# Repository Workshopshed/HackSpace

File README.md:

# HackSpace

Files to go with the Tutorials on HackSpace Magazine

## XMAS

Building a Bluetooth remote controlled Christmas light show

This project combines simple woodworking with electronics to produce a remote control Christmas decoration. Get yourself in the Christmas spirit from the comfort of your own armchair. The skills and techniques of this project can be used in a wide range of other projects.
The decoration is in the form of the 4 letters of XMAS. These are filled with green and red LEDs which are controlled by an Arduino.

https://hackspace.raspberrypi.org/issues/1

## MUSIC BOX

Marvellous mechanical music box

Another combination of woodwork and electronics, this time with no coding. Two 555 timers provide a monostable and astable to control a modified servo to drive a mechanical music mechanism. The stripboard design was done using KiCAD based on the following article.

https://hackspace.raspberrypi.org/issues/2 + https://hackspace.raspberrypi.org/features/the-book-of-making-volumn-1-out-now

https://hobbylad.wordpress.com/2013/04/26/designing-professional-looking-stripboards-using-kicad/ 

## GRINDER BOX

A silver soldered metal storage box to stop my angle grinder cables from being nibbled by mice.
Designed in Fusion360 and build using simple hand tools.

Font stencil from Jayde Garrow 
https://www.dafont.com/army-rust.font

https://hackspace.raspberrypi.org/issues/3 + https://hackspace.raspberrypi.org/features/the-book-of-making-volumn-1-out-now

## HACK SPACE SIGN

An EL Wire sign that lights up when there are people moving about in the room
Controlled using CircuitPython and an AdaFruit Trinket
Ultrabright EL Wire and drivers from EL Wire Craft

https://learn.adafruit.com/adafruit-trinket-m0-circuitpython-arduino/overview

https://hackspace.raspberrypi.org/issues/7 + https://hackspace.raspberrypi.org/features/the-book-of-making-volumn-1-out-now

## ROBOTIC WATER SENTRY

The robot water sentry uses the Google AIY Vision kit to detect humans an squirt them with water.

To make it easy to turn on and off there's a Pimoroni On/Off shim. After further research it was concluded that the default installer for this works just fine.

https://shop.pimoroni.com/products/onoff-shim

https://hackspace.raspberrypi.org/issues/9 + https://hackspace.raspberrypi.org/features/the-book-of-making-volumn-1-out-now

See also https://github.com/Workshopshed/JumboServo

## MONKEY SKULL BOWL

A simple project using the AdaFruit Gemma M0. Take care not to burn yourself when making the jewelled LED eyes.

https://hackspace.raspberrypi.org/issues/12

## KNIFE SWITCH

Unleash your inner mad scientist with this remote controlled knife switch. Using an Energenie remote control.

https://github.com/learn2develop/Arduino_Energenie_Pimote

https://hackspace.raspberrypi.org/issues/13

## ROUTER TRAY

When working with small components one of the best ways to store them for easy access is a shallow tray. So this project is a useful storage project made using a handheld router.

https://hackspace.raspberrypi.org/issues/13

## REMOTE DISPLAY

Show info and status from your home automation system with a low powered E-Ink display and MQTT.

https://hackspace.raspberrypi.org/issues/17

## BINARY KEYBOARD

By using a microcontroller that supports a HID (Human Interface Device) we can have a keyboard that lets you type the ASCII codes for the letters using just two keys a one and a zero

https://hackspace.raspberrypi.org/issues/18

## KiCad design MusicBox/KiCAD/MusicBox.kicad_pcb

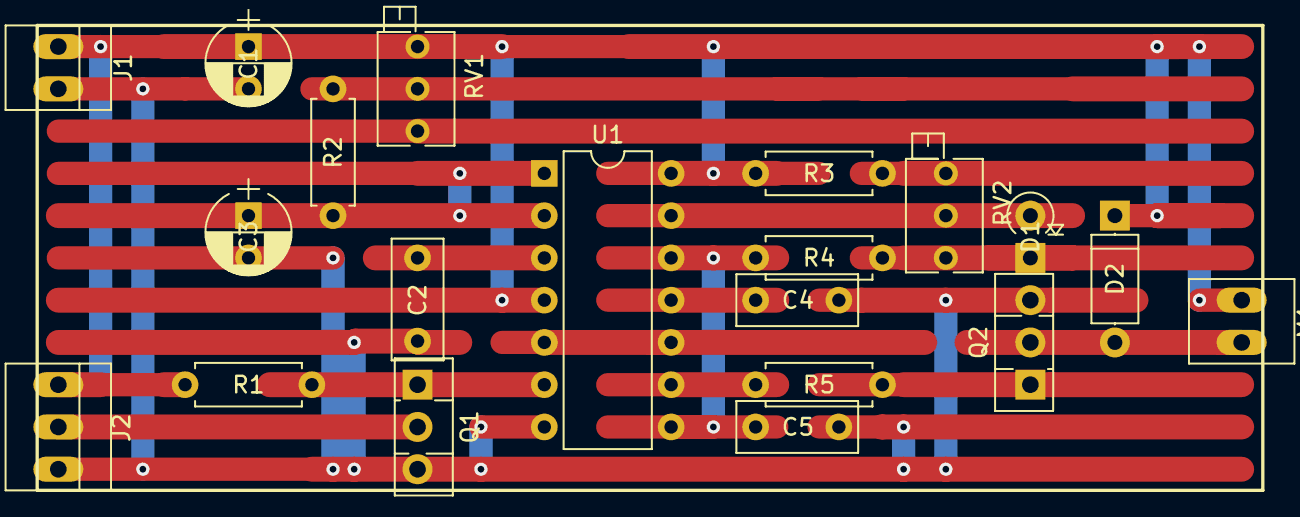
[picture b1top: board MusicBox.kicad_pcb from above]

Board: 2 copper layers, 20 parts (0 on the bottom side), 16 nets.

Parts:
C1, C3: 100uF; CP_Radial_D5.0mm_P2.00mm
C2, C4, C5: 10nF; C_Rect_L7.2mm_W3.0mm_P5.00mm_FKS2_FKP2_MKS2_MKP2
D1: D_ALT; D_A-405_P2.54mm_Vertical_KathodeUp
D2: D_ALT; D_A-405_P7.62mm_Horizontal
J1: Conn_01x02; PINHEAD1-2
J2: Conn_01x03; PINHEAD1-3
M1: Motor_DC; PINHEAD1-2
Q1: BC549; TO-126_Vertical
Q2: TIP31; TO-126_Vertical
R1, R3, R4, R5: 1K; R_Axial_DIN0207_L6.3mm_D2.5mm_P7.62mm_Horizontal
R2: 100K; R_Axial_DIN0207_L6.3mm_D2.5mm_P7.62mm_Horizontal
RV1, RV2: 100K; Potentiometer_Trimmer_Bourns_3266Z
U1: LM556; DIP-14_W7.62mm

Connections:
+BATT: C1.1, D2.1, J1.1, J2.1, M1.1, R1.1, R3.1, RV1.3, U1.4, U1.14
/Cap: J2.2, Q1.2
GND: C1.2, C2.2, C3.2, C4.2, C5.2, J1.2, J2.3, Q1.3, Q2.3, U1.7
unnamed: C2.1, U1.3
unnamed: C3.1, R2.2, U1.1, U1.2
unnamed: C4.1, U1.11
unnamed: C5.1, R4.2, U1.8, U1.12
unnamed: D2.2, M1.2, Q2.2
unnamed: D1.1, R4.1, RV2.1
unnamed: D1.2, RV2.2, U1.13
unnamed: Q1.1, R1.2, U1.6
unnamed: Q2.1, R5.1
unnamed: R2.1, RV1.2
unnamed: R3.2, RV2.3
unnamed: R5.2, U1.9
unnamed: U1.5, U1.10

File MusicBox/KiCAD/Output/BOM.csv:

"Id";"Designator";"Package";"Quantity";"Designation";"Supplier and ref";
1;"Q2";"TO-126_Vertical";1;"TIP31";;;
2;"RV1,RV2";"Potentiometer_Trimmer_Bourns_3266Z";2;"100K";;;
3;"U1";"DIP-14_W7.62mm";1;"LM556";;;
4;"C3,C1";"CP_Radial_D5.0mm_P2.00mm";2;"100uF";;;
5;"D2";"D_A-405_P7.62mm_Horizontal";1;"D_ALT";;;
6;"Q1";"TO-126_Vertical";1;"BC549";;;
7;"C2,C4,C5";"C_Rect_L7.2mm_W3.0mm_P5.00mm_FKS2_FKP2_MKS2_MKP2";3;"10nF";;;
8;"R2";"R_Axial_DIN0207_L6.3mm_D2.5mm_P7.62mm_Horizontal";1;"100K";;;
9;"R4,R3,R1,R5";"R_Axial_DIN0207_L6.3mm_D2.5mm_P7.62mm_Horizontal";4;"1K";;;
10;"M1";"PINHEAD1-2";1;"Motor_DC";;;
11;"J2";"PINHEAD1-3";1;"Conn_01x03";;;
12;"J1";"PINHEAD1-2";1;"Conn_01x02";;;
13;"D1";"D_DO-35_SOD27_P7.62mm_Horizontal";1;"D_ALT";;;

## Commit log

2017-11-23 XMAS
    Example code and a template
2017-11-25 Don't write the LEDs if not running
2017-12-21 MusicBox
2017-12-22 KiCAD
    Added KiCAD files
2017-12-22 Photo
2018-02-04 Grinder Box
    Fusion 3D model and generated plans for building this box
2018-05-29 HackSpace Sign
    Code and Schematic
2018-07-20 Robot Water Sentry
    A robot that squirts water
2018-07-20 Robot Water Sentry
    Updated Readme
2018-07-20 HackSpace Sign
    A glowing hackspace sign
2018-07-20 HackSpace Mag
    Added links to the various issues
2018-08-03 Servo
    Pulse on pin 13 so you can see that it's running
    Fixed issue where output pins for the L298 were not set
2018-10-16 Music Box Picture
    Updated picture to have better clipping
2018-10-17 Skull
    Skull Bowl
2018-10-17 Readme
    Skull section
2018-11-24 Knife Switch
    Knife Switch
2018-11-24 Knife Switch
    Knife Switch Readme
2018-11-24 Knife Switch
    Link to Energenie
2018-11-24 KnifeSwitch
    Code
2018-11-24 Knife Switch
    Renamed picture
2018-11-24 RouterTray
    Tray Pic
2018-11-28 Router Tray
    Picture for Router Tray
2019-03-13 RemoteDisplay
    Remote Display
2019-03-13 RemoteDisplay
    Pictures and diagrams
2019-03-15 Readme
    Remote Display
2019-03-23 Remote Display
    Moved the generation of the client ID out of the reconnect into the setup so the ID only changes at boot time
2019-04-22 Binary Keyboard
    Binary Keyboard
2019-04-22 Readme
    Binary Keyboard
2019-10-28 3D Models
